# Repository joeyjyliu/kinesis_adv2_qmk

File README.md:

# kinesis_adv2_qmk

# About
A drop-in PCB replacement for Kinesis Advantage2 keyboard for QMK firmware.

Based on the work from Stapelberg and Wunsch. What I have done is updating the thumb clusters connectors on the board. No more desoldering for the thumb clusters anymore on the Advantage2 keyboard. Just plug the connectors on the new board and you are ready to go for QMK firmware. If you want to revert it back, just replace the original PCB.

# Credits

Thanks to Stapelberg and Wunsch for their original work on the board for Advantage keyboard.

# Questions?

If you have questions or need an assembled kits/parts please contact me at joeyjyliu<remove_this> AT gmail.com.

# Donation

If this repo helps you, buy me a beer. :)

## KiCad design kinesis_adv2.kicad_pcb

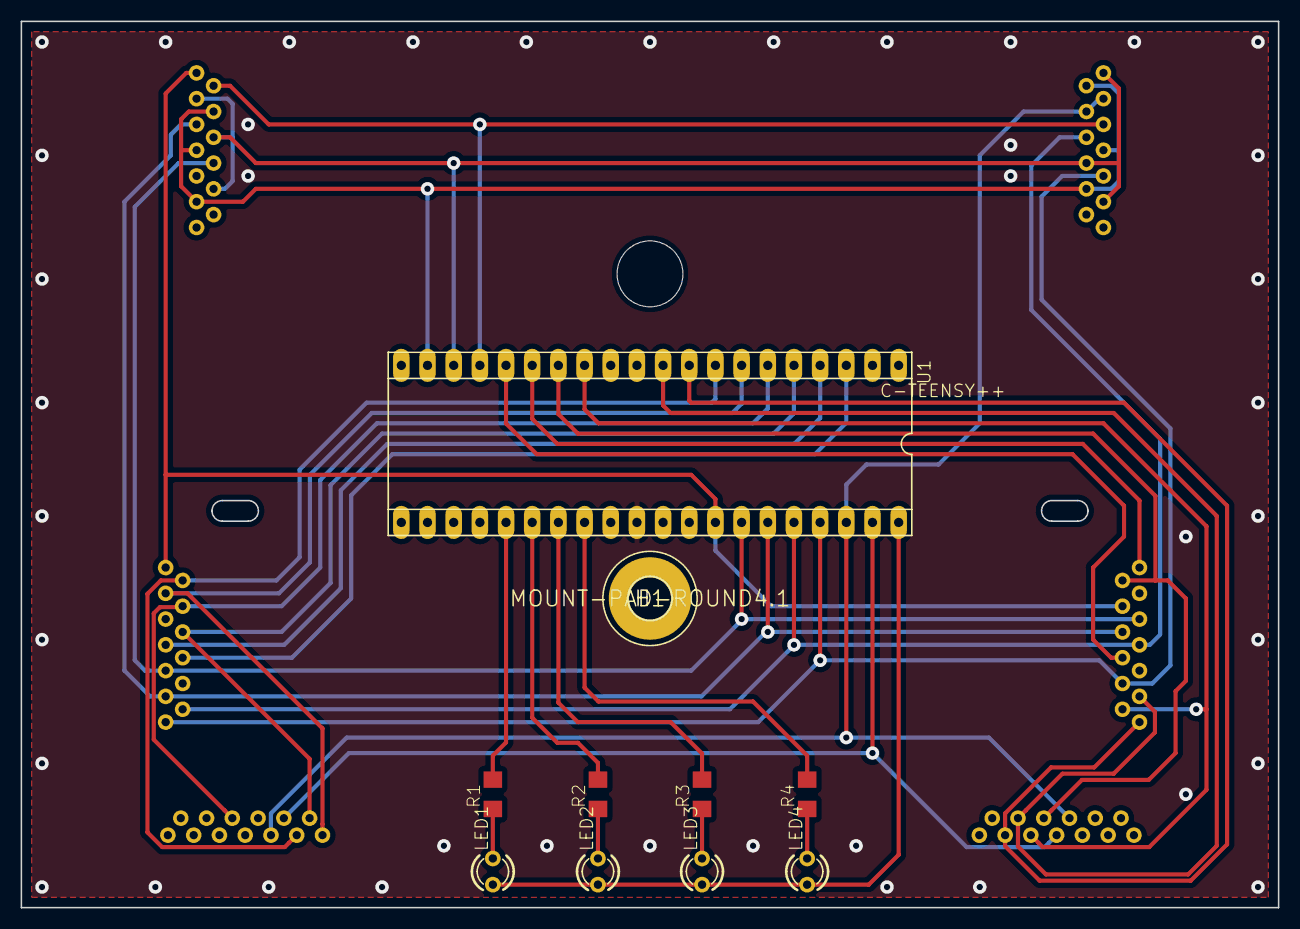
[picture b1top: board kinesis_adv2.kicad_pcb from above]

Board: 16 copper layers, 122.0 x 86.0 mm, 17 parts (0 on the bottom side), 31 nets.

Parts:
@HOLE0: (no value)
H1: MOUNT-PAD-ROUND4.1; 4,1-PAD
LED1, LED2, LED3, LED4: LED3MM
R1, R2, R3, R4: R1206
TASTENLINKS: 39-53-2355; 39-53-2135
TASTENLINKS#2, TASTENLINKS#3: 39-53-2355; 39-53-2135
TASTENRECHTS: 39-53-2355; 39-53-2135
TOPLINKS: 39-53-2355; 39-53-2135
TOPRECHTS: 39-53-2355; 39-53-2135
U1: C-TEENSY++; TEENSY++

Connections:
B0: TASTENLINKS.P$1, TASTENRECHTS.P$10, TOPLINKS.P$1, U1.B0
B1: TASTENLINKS.P$9, TASTENRECHTS.P$9, TOPLINKS.P$8, U1.B1
B2: TASTENLINKS.P$11, TASTENRECHTS.P$8, TOPLINKS.P$5, U1.B2
B3: TASTENLINKS.P$12, TASTENRECHTS.P$7, TOPRECHTS.P$8, U1.B3
B4: TASTENLINKS.P$13, TASTENRECHTS.P$4, TOPRECHTS.P$5, U1.B4
B5: TASTENLINKS#2.P$9, TASTENLINKS#3.P$8, TOPRECHTS.P$10, TOPRECHTS.P$11, U1.B5
B6: TASTENLINKS#2.P$10, TASTENLINKS#3.P$7, U1.B6
C0: TASTENLINKS#3.P$5, TASTENRECHTS.P$2, U1.C0
C1: TASTENLINKS#3.P$6, TASTENRECHTS.P$12, U1.C1
C2: TASTENRECHTS.P$13, U1.C2
C3: TASTENRECHTS.P$6, U1.C3
C4: TOPLINKS.P$2, TOPRECHTS.P$9, U1.C4
C5: TOPLINKS.P$3, TOPLINKS.P$6, TOPLINKS.P$10, TOPRECHTS.P$3, TOPRECHTS.P$6, TOPRECHTS.P$13, U1.C5
C6: TOPLINKS.P$4, TOPLINKS.P$7, TOPLINKS.P$11, TOPRECHTS.P$4, TOPRECHTS.P$7, TOPRECHTS.P$12, U1.C6
D0: TASTENLINKS.P$8, U1.D0
D1: TASTENLINKS.P$7, U1.D1
D2: TASTENLINKS.P$6, TASTENLINKS#2.P$12, U1.D2
D3: TASTENLINKS.P$4, TASTENLINKS#2.P$6, U1.D3
D4: TASTENLINKS.P$3, TASTENLINKS#2.P$13, U1.D4
D5: TASTENLINKS.P$2, TASTENLINKS#2.P$11, U1.D5
D6: TASTENLINKS#3.P$3, TASTENRECHTS.P$1, U1.D6
D7: TASTENLINKS#3.P$4, TASTENRECHTS.P$3, U1.D7
unnamed: R1.2, U1.F3
unnamed: R2.2, U1.F2
unnamed: R3.2, U1.F1
unnamed: R4.2, U1.F0
unnamed: LED1.A, LED2.A, LED3.A, LED4.A, U1.+5V
unnamed: LED4.K, R4.1
unnamed: LED3.K, R3.1
unnamed: LED2.K, R2.1
unnamed: LED1.K, R1.1

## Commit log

2018-06-02 initial revision
